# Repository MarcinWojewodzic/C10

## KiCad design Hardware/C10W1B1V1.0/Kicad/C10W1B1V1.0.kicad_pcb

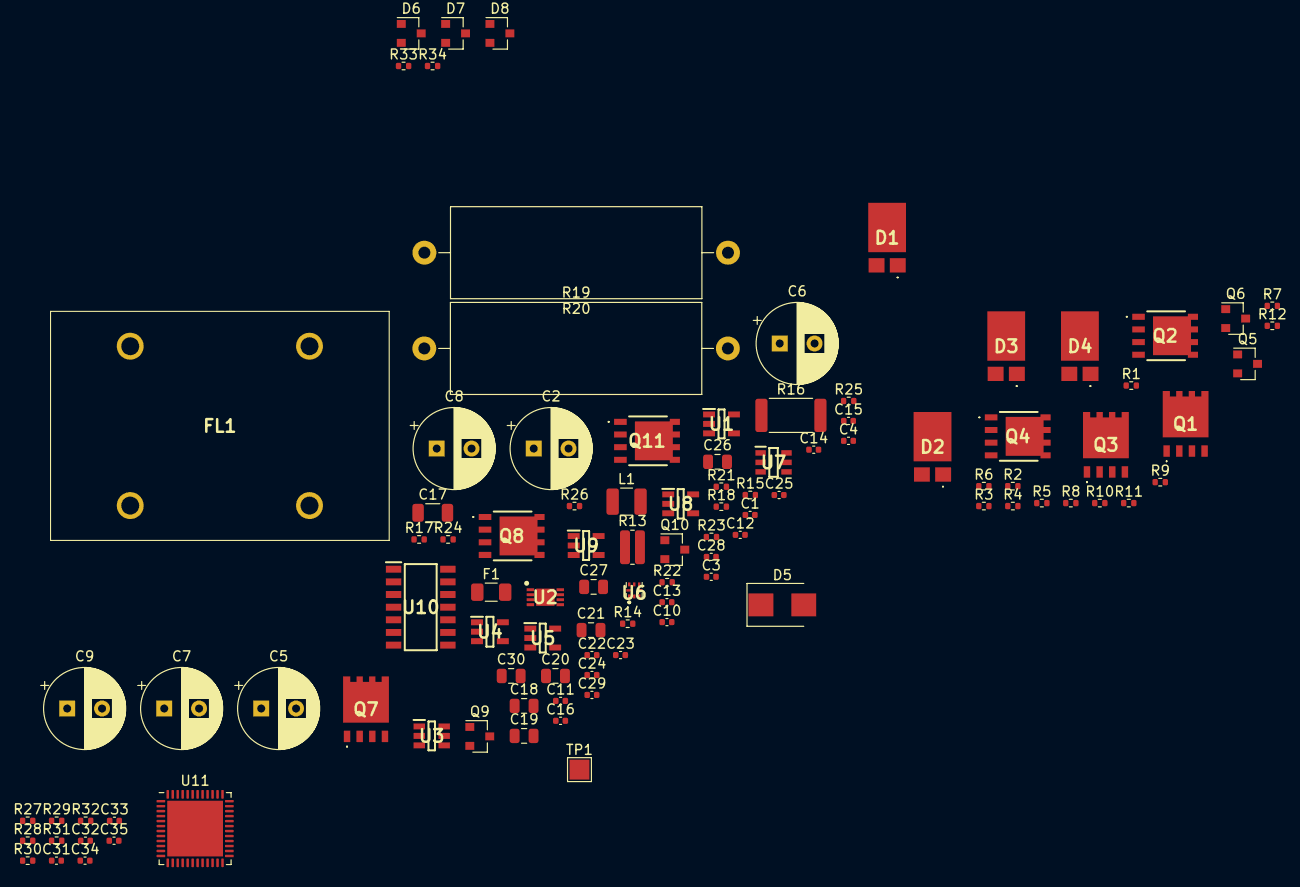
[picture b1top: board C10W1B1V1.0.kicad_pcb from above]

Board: 2 copper layers, 103 parts (0 on the bottom side), 45 nets, no tracks yet.

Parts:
C1, C10, C11, C12, C13, C14, C15, C16, C22: 100n/50V/X5R; C_0402_1005Metric
C2, C5, C6, C7, C8, C9: RGA101M1HBK-0811G; CP_Radial_D8.0mm_P3.50mm
C3, C4: 10n/50V/X5R; C_0402_1005Metric
C17: 10u/50V/X5R; C_1206_3216Metric
C18, C19, C20, C21, C26, C27, C30: 10u/10V/X5R; C_0805_2012Metric
C23, C28: 1u/50V/X5R; C_0402_1005Metric
C24: 100p/50V/X5R; C_0402_1005Metric
C25, C29: 2u2/50V/X5R; C_0402_1005Metric
C31, C32, C33, C34, C35: 4u7/50V/X5R; C_0402_1005Metric
D1, D2, D3, D4: PMEG45U10EPDZ
D5: D_TVS; D_SMB
D6, D7, D8: BAT54S; SOT-23
F1: SF-1206S1500W-2; Fuse_1206_3216Metric
FL1: SC-15-02J; SC1502J
L1: CBC3225T100KR; L_1210_3225Metric
Q1, Q3, Q7: STL300N4LF8; STL60N10F7
Q2, Q4, Q8, Q11: SI7155DP-T1-GE3; SI7155DPT1GE3
Q5, Q6, Q9, Q10: SQ2362CES-T1_GE3; SOT-23
R1, R8, R9, R12: 1K/1%/0.063W; R_0402_1005Metric
R2, R7, R10, R11, R21, R33: 100K/1%/0.063W; R_0402_1005Metric
R3, R5, R14, R17: 12K/1%/0.063W; R_0402_1005Metric
R4, R6, R15, R18: 22K/1%/0.063W; R_0402_1005Metric
R13: 10m/1%/0.063W; R_0612_1632Metric
R16: 50m/1%/0.063W; R_2512_6332Metric
R19, R20: 10/1%/5W; R_Axial_Power_L25.0mm_W9.0mm_P30.48mm
R22, R24, R25, R27, R28, R34: 10K/1%/0.063W; R_0402_1005Metric
R23: 3K3/1%/0.063W; R_0402_1005Metric
R26: 58.87K/1%/0.063W; R_0402_1005Metric
R29, R31: 174K/1%/0.063W; R_0402_1005Metric
R30, R32: 330K/1%/0.063W; R_0402_1005Metric
TP1: DC/DC; TestPoint_Pad_2.0x2.0mm
U1, U5: TSC101AILT; SOT95P280X145-5N
U2: MAX16171ATA_VY+; SON50P300X200X80-9N
U3: MCP1501T-20E/CHY; SOT95P280X145-6N
U4: AP331AWG-7; SOT95P285X145-5N
U6: NC7SZ74L8X
U7: AP64060QWU-7; SOT95P280X100-6N
U8: AP2210K-5.0TRG1; SOT95P282X145-5N
U9: TLV74333PDBVR; SOT95P280X145-5N
U10: 74HC08D,653; SOIC127P600X175-14N
U11: STM32L431CCUx; QFN-48-1EP_7x7mm_P0.5mm_EP5.6x5.6mm

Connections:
+3V3: C29.1, C30.1, C31.1, C32.1, C33.1, C34.1, C35.1, D6.2, D7.2, D8.2, R28.1, U9.5, U11.1, U11.9, U11.24, U11.36, U11.48
+5V: C10.1, C11.1, C12.1, C13.1, C14.2, C15.1, C25.1, C26.1, C27.1, C28.1, R23.1, R24.2, U1.5, U3.4, U3.6, U4.5, U5.5, U6.1, U6.6, U6.8, U8.4, U9.1, U9.3, U10.14
/H-Bridge/MOT+: D1.3, D2.1, D2.2, Q1.5, Q1.6, Q1.7, Q1.8, Q1.9, Q2.5, Q2.6, Q2.7, Q2.8, Q2.9, Q2.10, Q2.11
/H-Bridge/MOT-: D3.1, D3.2, D4.3, Q3.5, Q3.6, Q3.7, Q3.8, Q3.9, Q4.5, Q4.6, Q4.7, Q4.8, Q4.9, Q4.10, Q4.11
/Power And motor protection/~FLOP_OUT: U6.5, U10.2, U10.5, U10.10, U10.13
/uC/ADC_IN5: D7.3, R29.2, R30.1, U11.10
/uC/ADC_IN8: D6.3, R33.2, R34.1, U11.13
/uC/ADC_IN9: D8.3, R31.2, R32.1, U11.14
COMP_OUT: R22.2, R23.2, U4.4, U6.7, U11.41
FLOP_OUT: U6.3, U11.25
GND: C4.1, C5.2, C6.2, C7.2, C8.2, C9.2, C10.2, C11.2, C12.2, C13.2, C14.1, C15.2, C17.2, C18.2, C19.2, C20.2, C21.2, C22.2, C23.2, C24.2, C25.2, C26.2, C27.2, C28.2, C29.2, C30.2, C31.2, C32.2, C33.2, C34.2, C35.2, D1.1, D1.2, D4.1, D4.2, D6.1, D7.1, D8.1, FL1.3, Q1.1, Q1.2, Q1.3, Q3.1, Q3.2, Q3.3, Q5.2, Q6.2, Q9.2, Q10.2, R2.2, R7.2, R10.2, R11.2, R25.1, R27.2, R30.2, R32.2, R34.2, U1.2, U3.2, U3.3, U3.5, U4.2, U5.2, U6.4, U7.2, U8.2, U9.2, U10.7, U11.8, U11.23, U11.35, U11.47, U11.49
GND1: C1.2, C2.2, C3.2, D5.2, FL1.4, U2.5, U2.9
MAIN_CURRENT_SENSE: R29.1, U1.1, U4.1
unnamed: C1.1, D5.1, F1.1, Q7.1, Q7.2, Q7.3, U2.2, U2.3, U2.4
unnamed: C2.1, C3.1, FL1.1, Q7.5, Q7.6, Q7.7, Q7.8, Q7.9, U2.8
unnamed: C16.1, U7.1
unnamed: C16.2, L1.1, U7.6
unnamed: C18.1, C19.1, C20.1, C21.1, C22.1, C23.1, L1.2, R26.2, TP1.1, U8.1, U8.3
unnamed: C24.1, U8.5
unnamed: Q1.4, R9.1, R10.1
unnamed: Q2.4, R3.2, R4.2
unnamed: Q3.4, R11.1, R12.1
unnamed: Q4.4, R5.2, R6.2
unnamed: Q5.1, R1.1, R2.1
unnamed: Q5.3, R4.1
unnamed: Q6.1, R7.1, R8.1
unnamed: Q6.3, R6.1
unnamed: Q7.4, U2.1
unnamed: Q8.1, Q8.2, Q8.3, R13.2, R16.1, U1.4, U5.3
unnamed: Q8.4, R14.2, R15.2
unnamed: Q9.3, R15.1
unnamed: Q10.3, R18.1
unnamed: Q8.5, Q8.6, Q8.7, Q8.8, Q8.9, Q8.10, Q8.11, Q11.1, Q11.2, Q11.3, R16.2, R19.1, R20.2, U5.4
unnamed: Q11.4, R17.2, R18.2
unnamed: R21.1, U3.1
unnamed: R21.2, R22.1, U4.3
unnamed: R25.2, R26.1, U7.3
unnamed: R27.1, U11.44
unnamed: R28.2, U11.7
SHORT_RANGE_CURRENT_SENSE: R31.1, U5.1
SHORT_RANGE_CURRENT_SENSE_EN: Q9.1, U11.33
STARTUP_ENABLE: Q10.1, U11.46
VCC: C4.2, C5.1, C6.1, C7.1, C8.1, C9.1, C17.1, FL1.2, R3.1, R5.1, R13.1, R14.1, R17.1, R33.1, U1.3, U7.4, U7.5
Vdrive: D2.3, D3.3, Q2.1, Q2.2, Q2.3, Q4.1, Q4.2, Q4.3, Q11.5, Q11.6, Q11.7, Q11.8, Q11.9, Q11.10, Q11.11, R19.2, R20.1
~FLOP_RST: R24.1, U6.2, U11.45

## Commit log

2025-02-09 Initial
2025-02-13 Mostek H
2025-02-18 Dodano zabezpieczenia
